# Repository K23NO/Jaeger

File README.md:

# Jaeger

Differential-drive mobile robot (TETRIX MAX) with a two-degree-of-freedom ball-balancing platform,
used to study the transport of an unsecured load. Course project of Mechatronic Systems Design
(MT5001), Universidad de Ingeniería y Tecnología (UTEC), Lima, 2026-2.

Authors: Flavia Sofía Díaz Follegatti, Flavia Luciana Palacios Davalos, Brenda De la Cruz Menacho,
Kenyi Reyes De Lama.

## System

| Unit | Role |
|---|---|
| NI myRIO-1900 (LabVIEW 2019) | Runs both control loops: cascaded speed/position control of the base every 10 ms and two-axis PID of the ball position at the camera rate |
| Raspberry Pi 3 + Logitech Brio | Detects the ball at 60 fps and sends `x, y` in mm to the myRIO over UART (230 400 baud) |
| ESP32 (bench only) | Logged the motor and servo step responses used for plant identification |

## Repository layout

```
hardware/
  pcb_myrio_interface/      KiCad project, BOM, STEP and Gerber/drill files of the interface board (board 1)
  pcb_touch_panel_unused/   Touch-panel interface board (board 2); designed but not used in the final prototype
  mechanical/               Exploded-view drawings of the assembly
software/
  myrio_labview/            LabVIEW project (Main.vi): base and plate controllers, logging
  raspberry_vision/         Ball detection, px-to-mm calibration, UART sender, setup script and service
  esp32_bench/              Arduino sketches and Python loggers for plant identification
data/
  identification_motors/            Motor speed response to PWM steps (2026-10-17)
  identification_plate_servos/      Plate tilt response to servo steps (2026-10-19)
  integration_2026-11-17/raw/       LabVIEW logs of the integrated trials (level-floor routine and 10° ramp)
  integration_2026-11-17/clean/     Same logs as CSV with headers fixed and time aligned to the first base set-point
analysis/                   Scripts that produce the figures and metrics of the report
docs/                       Design notes (electronics plan, camera setup, UART protocol, PID review)
```

3D-printable and laser-cut parts of the balancing platform: Mendeley Data,
doi:[10.17632/638z9y6dd9.1](https://doi.org/10.17632/638z9y6dd9.1).

## Data notes

* Plate logs: the LabVIEW header is shifted. Ball position is in columns `inclinacion_x` (x, mm) and
  `inclinacion_y` (y, mm); `erro_x`/`error_y` repeat them because the reference is 0.
* Plate logs have no time column and their period varies between runs (9–15 ms), so plate and base
  logs are not aligned in time.
* Metrics discard the first 300 plate samples after the ball is first detected (ball placement).

## Licenses

Software: MIT (`LICENSE`). Hardware design files and documentation: CC BY 4.0 (`LICENSE-hardware.md`).

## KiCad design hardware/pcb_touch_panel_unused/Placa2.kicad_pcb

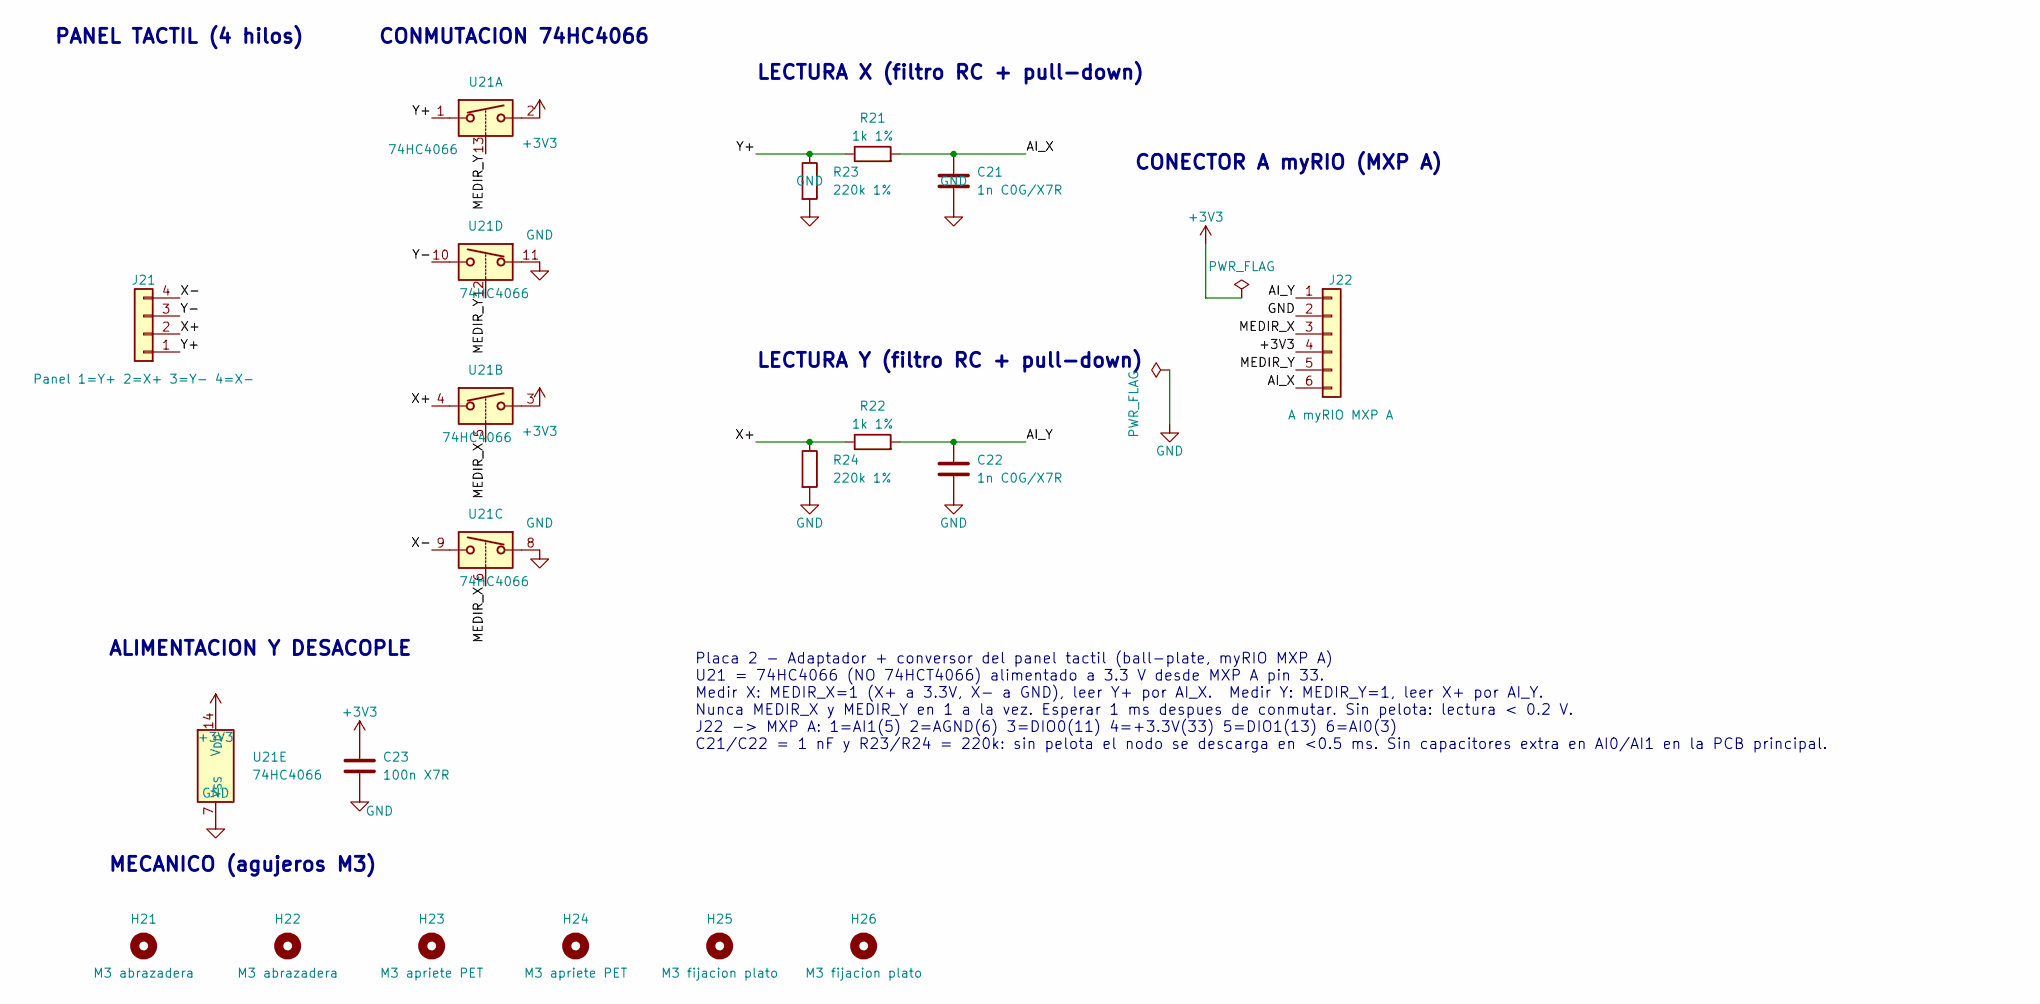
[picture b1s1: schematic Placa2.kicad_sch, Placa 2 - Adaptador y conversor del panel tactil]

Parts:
C21, C22: 1n C0G/X7R; C_Disc_D5.0mm_W2.5mm_P5.00mm
C23: 100n X7R; C_Disc_D5.0mm_W2.5mm_P5.00mm
H21, H22: M3 abrazadera; MountingHole_3.2mm_M3
H23, H24: M3 apriete PET; MountingHole_3.2mm_M3
H25, H26: M3 fijacion plato; MountingHole_3.2mm_M3
J21: Panel 1=Y+ 2=X+ 3=Y- 4=X-; Panel_FPC_4P_P1.0mm_Presion
J22: A myRIO MXP A; PinHeader_1x06_P2.54mm_Vertical
R21, R22: 1k 1%; R_Axial_DIN0207_L6.3mm_D2.5mm_P10.16mm_Horizontal
R23, R24: 220k 1%; R_Axial_DIN0207_L6.3mm_D2.5mm_P10.16mm_Horizontal
U21: 74HC4066; DIP-14_W7.62mm_Socket_LongPads

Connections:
+3V3: C23.1, J22.4, U21.2, U21.3, U21.14 (V_{DD})
/AI_X: C21.1, J22.6, R21.2
/AI_Y: C22.1, J22.1, R22.2
/MEDIR_X: J22.3, U21.5, U21.6
/MEDIR_Y: J22.5, U21.12, U21.13
/X+: J21.2, R22.1, R24.1, U21.4
/X-: J21.4, U21.9
/Y+: J21.1, R21.1, R23.1, U21.1
/Y-: J21.3, U21.10
GND: C21.2, C22.2, C23.2, J22.2, R23.2, R24.2, U21.7 (V_{SS}), U21.8, U21.11

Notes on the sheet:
MECANICO (agujeros M3)
PANEL TACTIL (4 hilos)
Placa 2 - Adaptador + conversor del panel tactil (ball-plate, myRIO MXP A) U21 = 74HC4066 (NO 74HCT4066) alimentado a 3.3 V desde MXP A pin 33. Medir X: MEDIR_X=1 (X+ a 3.3V, X- a GND), leer Y+ por AI_X. Medir Y: MEDIR_Y=1, leer X+ por AI_Y. Nunca MEDIR_X y MEDIR_Y en 1 a la vez. Esperar 1 ms despu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
CONMUTACION 74HC4066
ALIMENTACION Y DESACOPLE
LECTURA Y (filtro RC + pull-down)
LECTURA X (filtro RC + pull-down)
CONECTOR A myRIO (MXP A)

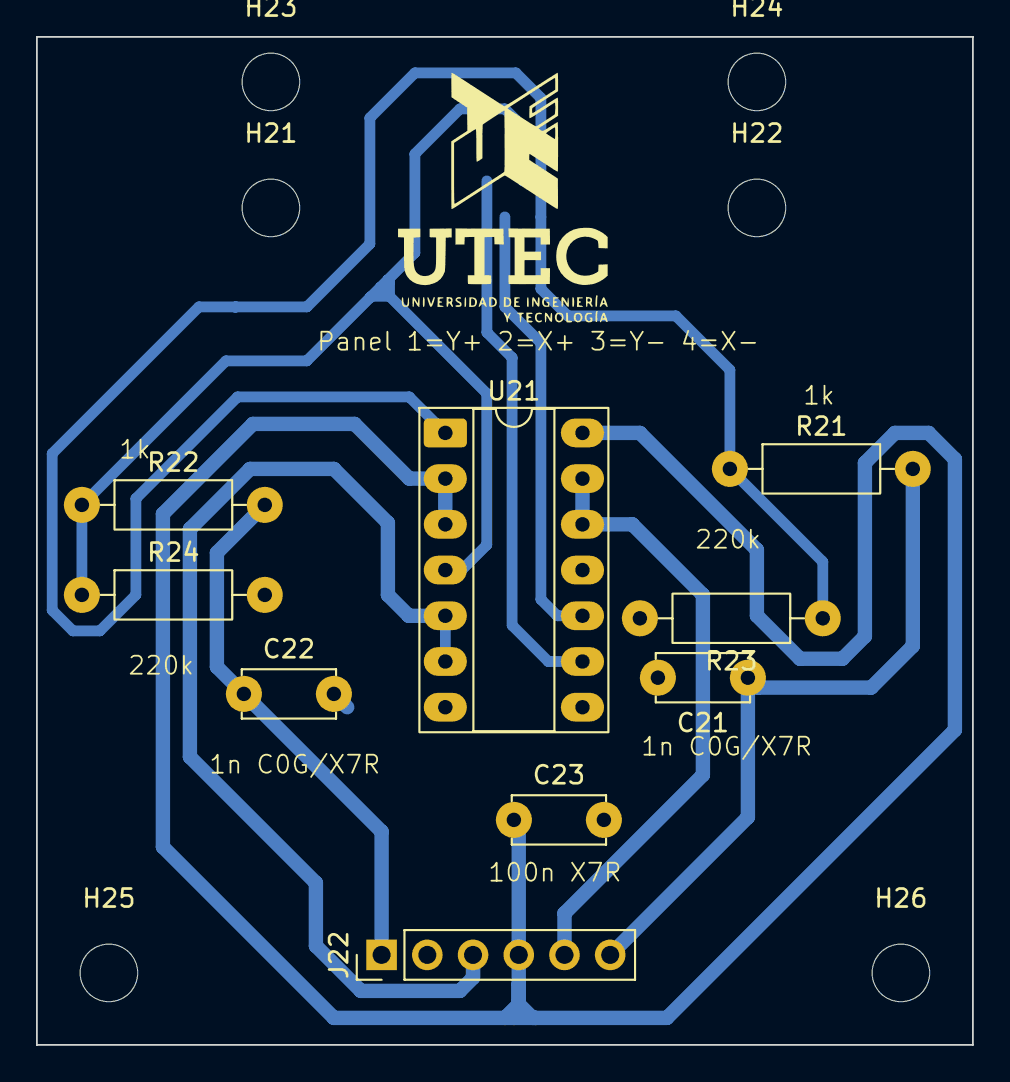
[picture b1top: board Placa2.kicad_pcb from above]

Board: 2 copper layers, 52.0 x 56.0 mm, 16 parts (1 on the bottom side), 10 nets.

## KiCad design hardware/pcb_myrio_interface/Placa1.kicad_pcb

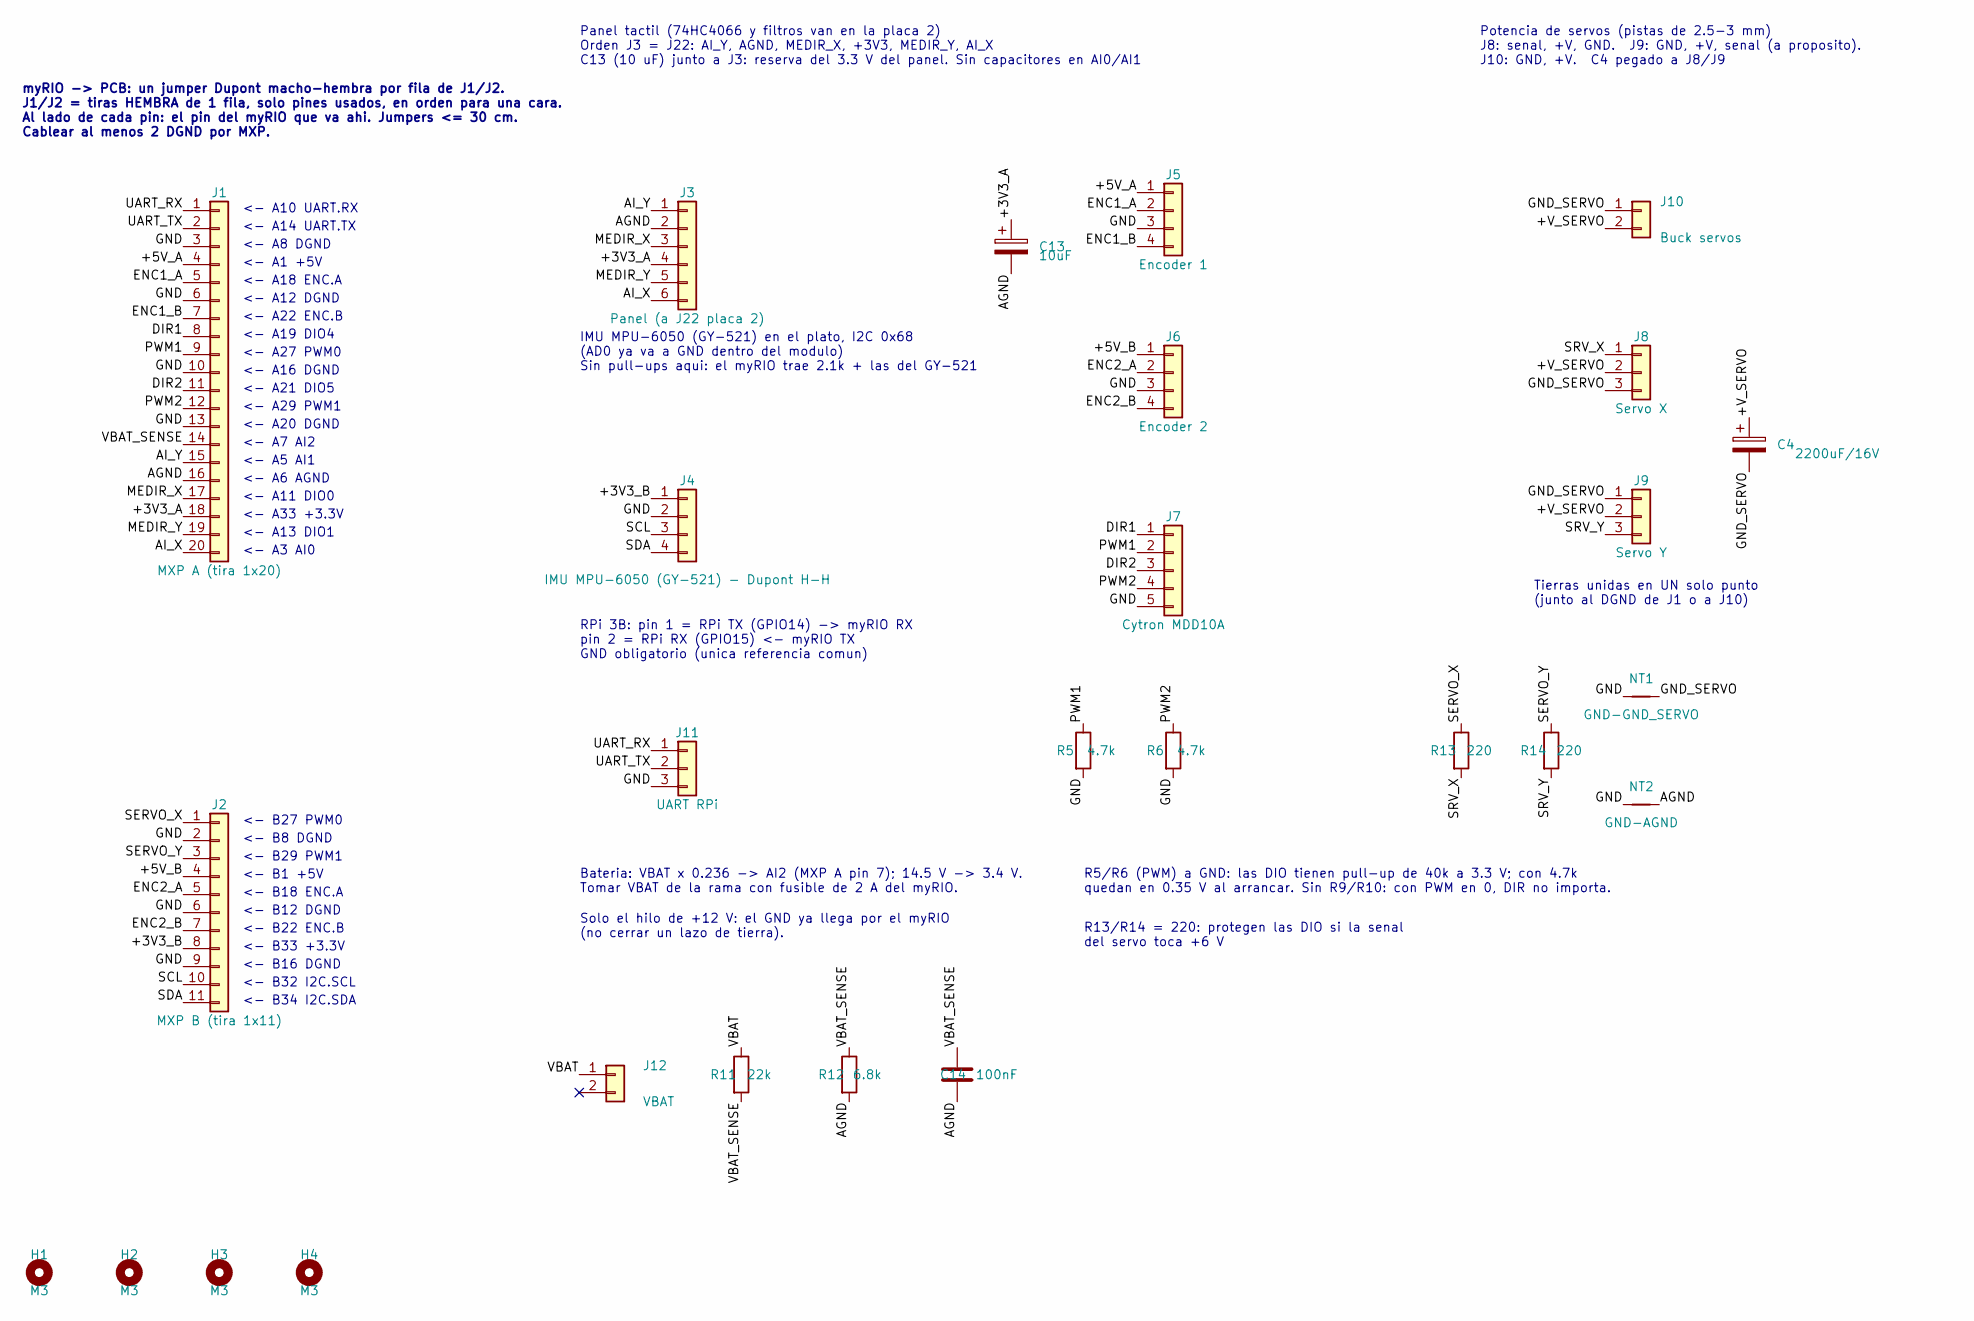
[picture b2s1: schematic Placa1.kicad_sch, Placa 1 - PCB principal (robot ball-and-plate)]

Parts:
C4: 2200uF/16V; CP_Radial_D13.0mm_P5.00mm
C13: 10uF; CP_Radial_D5.0mm_P2.50mm; Voltage 16V
C14: 100nF; C_Disc_D5.0mm_W2.5mm_P5.00mm
H1, H2, H3, H4: M3; MountingHole_3.2mm_M3
J1: MXP A (tira 1x20); PinSocket_1x20_P2.54mm_Vertical
J2: MXP B (tira 1x11); PinSocket_1x11_P2.54mm_Vertical
J3: Panel (a J22 placa 2); PinHeader_1x06_P2.54mm_Vertical
J4: IMU MPU-6050 (GY-521) - Dupont H-H; PinHeader_1x04_P2.54mm_Vertical
J5: Encoder 1; TerminalBlock_Phoenix_PT-1,5-4-3.5-H_1x04_P3.50mm_Horizontal
J6: Encoder 2; TerminalBlock_Phoenix_PT-1,5-4-3.5-H_1x04_P3.50mm_Horizontal
J7: Cytron MDD10A; TerminalBlock_Phoenix_PT-1,5-5-3.5-H_1x05_P3.50mm_Horizontal
J8: Servo X; TerminalBlock_Phoenix_PT-1,5-3-3.5-H_1x03_P3.50mm_Horizontal
J9: Servo Y; TerminalBlock_Phoenix_PT-1,5-3-3.5-H_1x03_P3.50mm_Horizontal
J10: Buck servos; TerminalBlock_MaiXu_MX126-5.0-02P_1x02_P5.00mm
J11: UART RPi; TerminalBlock_Phoenix_PT-1,5-3-3.5-H_1x03_P3.50mm_Horizontal
J12: VBAT; TerminalBlock_Phoenix_PT-1,5-2-3.5-H_1x02_P3.50mm_Horizontal
NT1: GND-GND_SERVO; NetTie-2_THT_Pad1.0mm
NT2: GND-AGND; NetTie-2_THT_Pad1.0mm
R5, R6: 4.7k; R_Axial_DIN0207_L6.3mm_D2.5mm_P10.16mm_Horizontal
R11: 22k; R_Axial_DIN0207_L6.3mm_D2.5mm_P10.16mm_Horizontal
R12: 6.8k; R_Axial_DIN0207_L6.3mm_D2.5mm_P10.16mm_Horizontal
R13, R14: 220; R_Axial_DIN0207_L6.3mm_D2.5mm_P10.16mm_Horizontal

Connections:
/+3V3_A: C13.1, J1.18, J3.4
/+3V3_B: J2.8, J4.1
/+5V_A: J1.4, J5.1
/+5V_B: J2.4, J6.1
/+V_SERVO: C4.1, J8.2, J9.2, J10.2
/AGND: C13.2, C14.2, J1.16, J3.2, NT2.2, R12.2
/AI_X: J1.20, J3.6
/AI_Y: J1.15, J3.1
/DIR1: J1.8, J7.1
/DIR2: J1.11, J7.3
/ENC1_A: J1.5, J5.2
/ENC1_B: J1.7, J5.4
/ENC2_A: J2.5, J6.2
/ENC2_B: J2.7, J6.4
/GND: J1.3, J1.6, J1.10, J1.13, J2.2, J2.6, J2.9, J4.2, J5.3, J6.3, J7.5, J11.3, NT1.1, NT2.1, R5.2, R6.2
/GND_SERVO: C4.2, J8.3, J9.1, J10.1, NT1.2
/MEDIR_X: J1.17, J3.3
/MEDIR_Y: J1.19, J3.5
/PWM1: J1.9, J7.2, R5.1
/PWM2: J1.12, J7.4, R6.1
/SCL: J2.10, J4.3
/SDA: J2.11, J4.4
/SERVO_X: J2.1, R13.1
/SERVO_Y: J2.3, R14.1
/SRV_X: J8.1, R13.2
/SRV_Y: J9.3, R14.2
/UART_RX: J1.1, J11.1
/UART_TX: J1.2, J11.2
/VBAT: J12.1, R11.1
/VBAT_SENSE: C14.1, J1.14, R11.2, R12.1

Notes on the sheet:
R5/R6 (PWM) a GND: las DIO tienen pull-up de 40k a 3.3 V; con 4.7k quedan en 0.35 V al arrancar. Sin R9/R10: con PWM en 0, DIR no importa.
Potencia de servos (pistas de 2.5-3 mm) J8: senal, +V, GND. J9: GND, +V, senal (a proposito). J10: GND, +V. C4 pegado a J8/J9
myRIO -> PCB: un jumper Dupont macho-hembra por fila de J1/J2. J1/J2 = tiras HEMBRA de 1 fila, solo pines usados, en orden para una cara. Al lado de cada pin: el pin del myRIO que va ahi. Jumpers <= 30 cm. Cablear al menos 2 DGND por MXP.
IMU MPU-6050 (GY-521) en el plato, I2C 0x68 (AD0 ya va a GND dentro del modulo) Sin pull-ups aqui: el myRIO trae 2.1k + las del GY-521
RPi 3B: pin 1 = RPi TX (GPIO14) -> myRIO RX pin 2 = RPi RX (GPIO15) <- myRIO TX GND obligatorio (unica referencia comun)
Panel tactil (74HC4066 y filtros van en la placa 2) Orden J3 = J22: AI_Y, AGND, MEDIR_X, +3V3, MEDIR_Y, AI_X C13 (10 uF) junto a J3: reserva del 3.3 V del panel. Sin capacitores en AI0/AI1
Tierras unidas en UN solo punto (junto al DGND de J1 o a J10)
Bateria: VBAT x 0.236 -> AI2 (MXP A pin 7); 14.5 V -> 3.4 V. Tomar VBAT de la rama con fusible de 2 A del myRIO.
Solo el hilo de +12 V: el GND ya llega por el myRIO (no cerrar un lazo de tierra).
R13/R14 = 220: protegen las DIO si la senal del servo toca +6 V
<- A10 UART.RX
<- A14 UART.TX
<- A8 DGND
<- A1 +5V
<- A18 ENC.A
<- A12 DGND
<- A22 ENC.B
<- A19 DIO4
<- A27 PWM0
<- A16 DGND
<- A21 DIO5
<- A29 PWM1
<- A20 DGND
<- A7 AI2
<- A5 AI1
<- A6 AGND
<- A11 DIO0
<- A33 +3.3V
<- A13 DIO1
<- A3 AI0
<- B27 PWM0
<- B8 DGND
<- B29 PWM1
<- B1 +5V
<- B18 ENC.A
<- B12 DGND
<- B22 ENC.B
<- B33 +3.3V
<- B16 DGND
<- B32 I2C.SCL

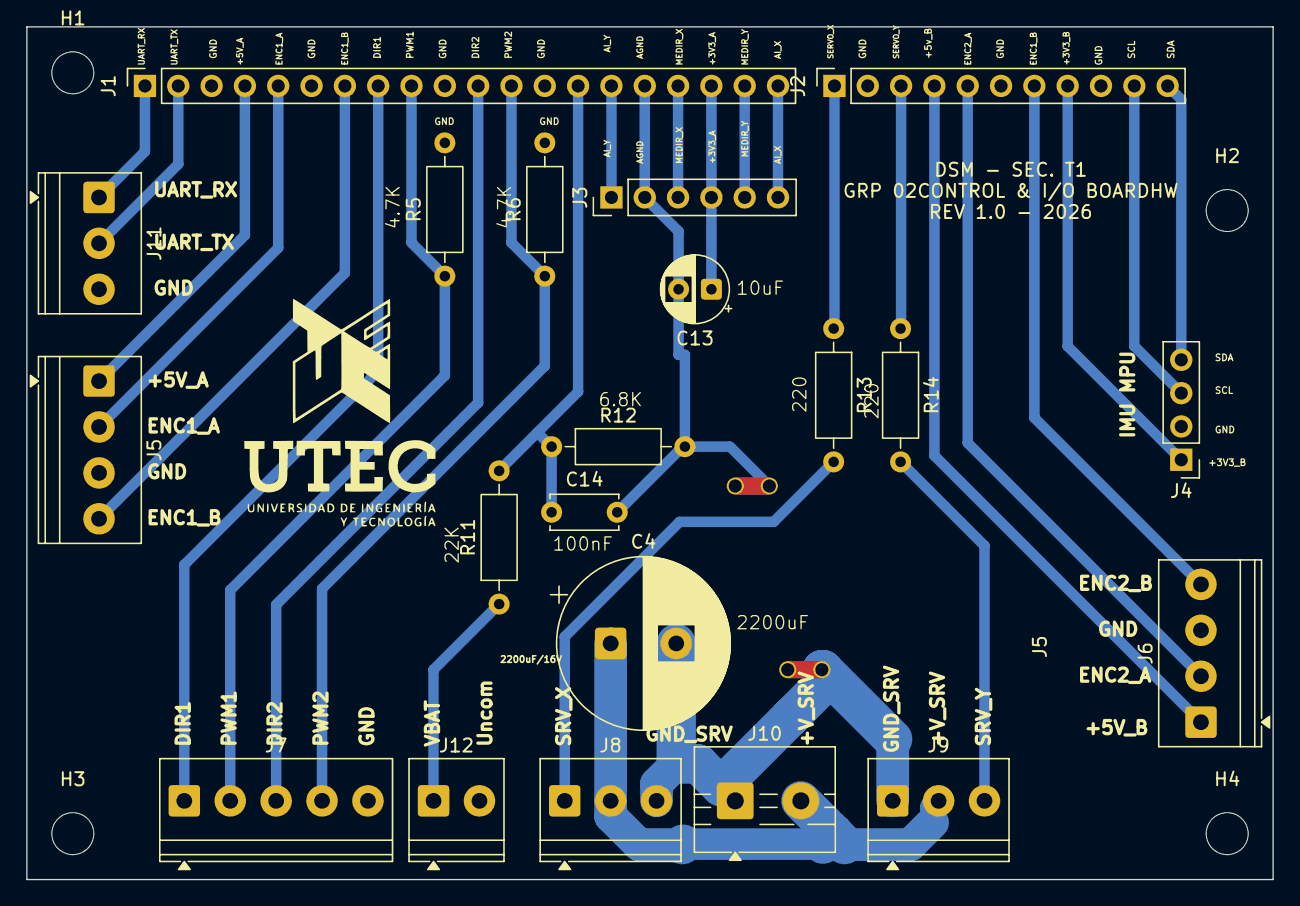
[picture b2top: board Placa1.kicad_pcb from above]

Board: 2 copper layers, 95.0 x 65.0 mm, 27 parts (0 on the bottom side), 30 nets.

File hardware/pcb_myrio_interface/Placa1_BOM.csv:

"Referencias","Valor","Huella","Cantidad"
"C4","2200uF/16V","Capacitor_THT:CP_Radial_D13.0mm_P5.00mm","1"
"C13","10uF","Capacitor_THT:CP_Radial_D5.0mm_P2.50mm","1"
"C14","100nF","Capacitor_THT:C_Disc_D5.0mm_W2.5mm_P5.00mm","1"
"H1-H4","M3","MountingHole:MountingHole_3.2mm_M3","4"
"J1","MXP A (tira 1x20)","Connector_PinSocket_2.54mm:PinSocket_1x20_P2.54mm_Vertical","1"
"J2","MXP B (tira 1x11)","Connector_PinSocket_2.54mm:PinSocket_1x11_P2.54mm_Vertical","1"
"J3","Panel (a J22 placa 2)","Connector_PinHeader_2.54mm:PinHeader_1x06_P2.54mm_Vertical","1"
"J4","IMU MPU-6050 (GY-521) - Dupont H-H","Connector_PinHeader_2.54mm:PinHeader_1x04_P2.54mm_Vertical","1"
"J5","Encoder 1","TerminalBlock_Phoenix:TerminalBlock_Phoenix_PT-1,5-4-3.5-H_1x04_P3.50mm_Horizontal","1"
"J6","Encoder 2","TerminalBlock_Phoenix:TerminalBlock_Phoenix_PT-1,5-4-3.5-H_1x04_P3.50mm_Horizontal","1"
"J7","Cytron MDD10A","TerminalBlock_Phoenix:TerminalBlock_Phoenix_PT-1,5-5-3.5-H_1x05_P3.50mm_Horizontal","1"
"J8","Servo X","TerminalBlock_Phoenix:TerminalBlock_Phoenix_PT-1,5-3-3.5-H_1x03_P3.50mm_Horizontal","1"
"J9","Servo Y","TerminalBlock_Phoenix:TerminalBlock_Phoenix_PT-1,5-3-3.5-H_1x03_P3.50mm_Horizontal","1"
"J10","Buck servos","TerminalBlock:TerminalBlock_MaiXu_MX126-5.0-02P_1x02_P5.00mm","1"
"J11","UART RPi","TerminalBlock_Phoenix:TerminalBlock_Phoenix_PT-1,5-3-3.5-H_1x03_P3.50mm_Horizontal","1"
"J12","VBAT","TerminalBlock_Phoenix:TerminalBlock_Phoenix_PT-1,5-2-3.5-H_1x02_P3.50mm_Horizontal","1"
"NT1","GND-GND_SERVO","NetTie:NetTie-2_THT_Pad1.0mm","1"
"NT2","GND-AGND","NetTie:NetTie-2_THT_Pad1.0mm","1"
"R5,R6","4.7k","Resistor_THT:R_Axial_DIN0207_L6.3mm_D2.5mm_P10.16mm_Horizontal","2"
"R11","22k","Resistor_THT:R_Axial_DIN0207_L6.3mm_D2.5mm_P10.16mm_Horizontal","1"
"R12","6.8k","Resistor_THT:R_Axial_DIN0207_L6.3mm_D2.5mm_P10.16mm_Horizontal","1"
"R13,R14","220","Resistor_THT:R_Axial_DIN0207_L6.3mm_D2.5mm_P10.16mm_Horizontal","2"

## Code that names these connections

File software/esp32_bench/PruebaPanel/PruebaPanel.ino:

// ========== PRUEBA DEL PANEL TACTIL RESISTIVO DE 4 HILOS (ESP32 DevKit) ==========
// Ver Project_ball/Electronica/plan_electronica.md, seccion 1.
//
// Dos modos (elegir con MODO):
//   DIRECTO  El ESP32 maneja los 4 terminales del panel con sus pines (sin 74HC4066).
//            Sirve para probar el panel y su conector antes de armar la placa.
//   SWITCH   El panel va a traves de la placa con el 74HC4066 (como en el myRIO).
//
// En los dos modos, poner R 100 kOhm de cada linea de lectura a GND (pull-down):
// sin pelota, la lectura cae a ~0 V y asi se detecta "sin toque".
//
// Monitor Serie a 115200. Imprime cada 20 ms:  vx_mV,vy_mV,tocado
// Para calibrar: anotar vx_mV y vy_mV con la pelota en las 4 esquinas del area util.

#include <Arduino.h>

#define DIRECTO 0
#define SWITCH  1
#define MODO    DIRECTO

// ---------------- Pines modo DIRECTO ----------------
// X+ e Y+ se usan como salida Y como entrada analogica: tienen que ser ADC1 con salida (32, 33).
const int XP = 32;   // X+
const int YP = 33;   // Y+
const int XM = 25;   // X-
const int YM = 26;   // Y-

// ---------------- Pines modo SWITCH ----------------
const int MEDIR_X = 25;   // -> ctrl-A y ctrl-B del 74HC4066
const int MEDIR_Y = 26;   // -> ctrl-C y ctrl-D
const int AI_X = 34;      // <- Y+ (a traves de 1 kOhm)
const int AI_Y = 35;      // <- X+ (a traves de 1 kOhm)

const uint32_t ESPERA_US = 1000;   // estabilizacion despues de cambiar de eje
const uint32_t PERIODO_MS = 20;
const int UMBRAL_MV = 50;          // por debajo: sin toque

void soltarTodo() {
  pinMode(XP, INPUT);
  pinMode(YP, INPUT);
  pinMode(XM, INPUT);
  pinMode(YM, INPUT);
}

int leerDirecto(bool ejeX) {
  soltarTodo();
  int alto = ejeX ? XP : YP, bajo = ejeX ? XM : YM, lectura = ejeX ? YP : XP;
  pinMode(alto, OUTPUT);
  digitalWrite(alto, HIGH);
  pinMode(bajo, OUTPUT);
  digitalWrite(bajo, LOW);
  delayMicroseconds(ESPERA_US);
  int mv = analogReadMilliVolts(lectura);
  soltarTodo();
  return mv;
}

int leerSwitch(bool ejeX) {
  digitalWrite(MEDIR_X, LOW);   // nunca las dos capas polarizadas a la vez
  digitalWrite(MEDIR_Y, LOW);
  digitalWrite(ejeX ? MEDIR_X : MEDIR_Y, HIGH);
  delayMicroseconds(ESPERA_US);
  int mv = analogReadMilliVolts(ejeX ? AI_X : AI_Y);
  digitalWrite(ejeX ? MEDIR_X : MEDIR_Y, LOW);
  return mv;
}

void setup() {
  Serial.begin(115200);
  analogReadResolution(12);
  analogSetAttenuation(ADC_11db);   // rango ~0-3.1 V
#if MODO == SWITCH
  pinMode(MEDIR_X, OUTPUT);
  pinMode(MEDIR_Y, OUTPUT);
  digitalWrite(MEDIR_X, LOW);
  digitalWrite(MEDIR_Y, LOW);
  Serial.println("# Modo SWITCH (74HC4066)");
#else
  soltarTodo();
  Serial.println("# Modo DIRECTO (ESP32 maneja el panel)");
#endif
  Serial.println("vx_mV,vy_mV,tocado");
}

void loop() {
  static uint32_t t_prev = 0;
  if (millis() - t_prev < PERIODO_MS) return;
  t_prev = millis();

#if MODO == SWITCH
  int vx = leerSwitch(true);
  int vy = leerSwitch(false);
#else
  int vx = leerDirecto(true);
  int vy = leerDirecto(false);
#endif
  bool tocado = vx > UMBRAL_MV && vy > UMBRAL_MV;

  Serial.print(vx);
  Serial.print(',');
  Serial.print(vy);
  Serial.print(',');
  Serial.println(tocado ? 1 : 0);
}
